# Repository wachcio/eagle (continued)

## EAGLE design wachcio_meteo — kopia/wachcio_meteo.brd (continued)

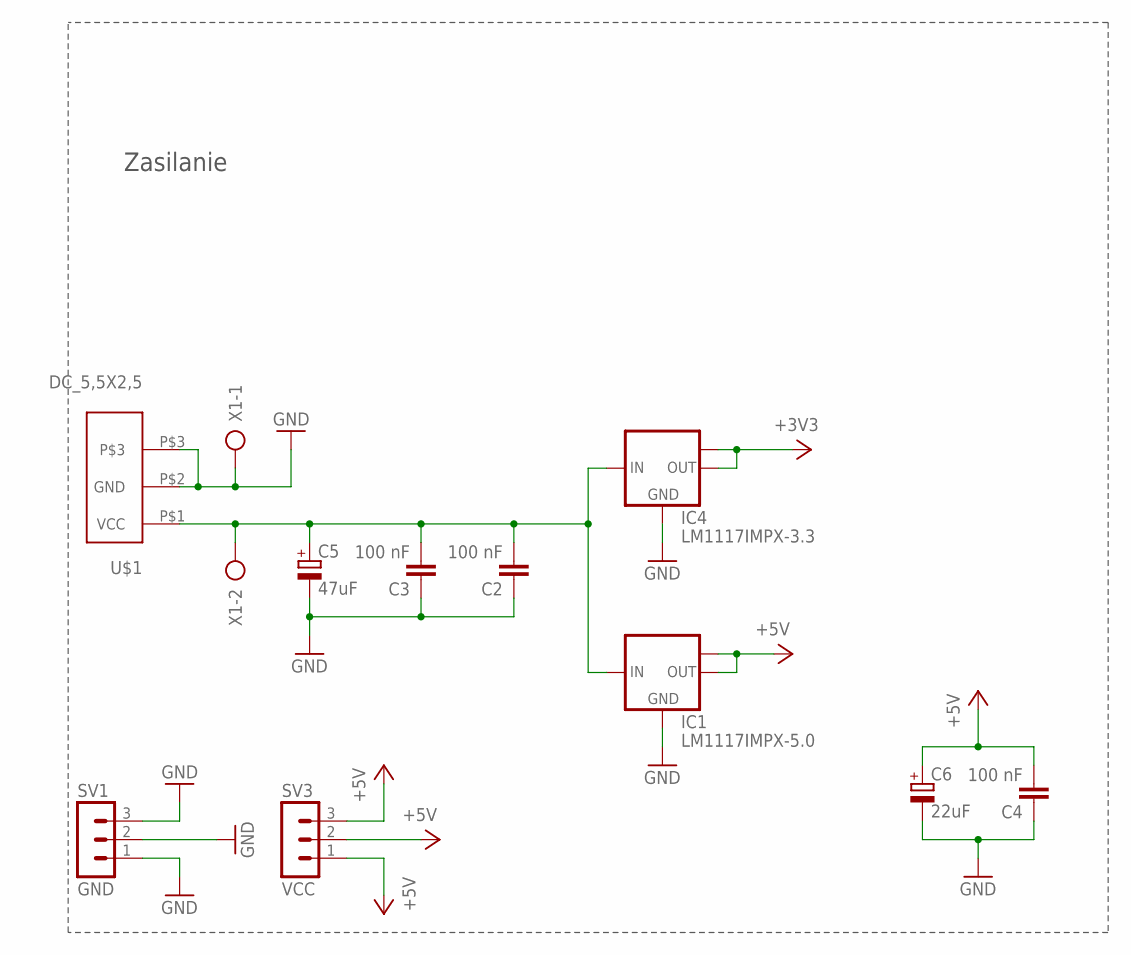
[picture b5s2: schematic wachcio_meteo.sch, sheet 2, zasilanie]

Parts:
C2, C3, C4: 100 nF; C0805
C5: 47uF; B45181A
C6: 22uF; B45181A
IC1: LM1117IMPX-5.0; SOT223
IC4: LM1117IMPX-3.3; SOT223
SV1: GND; MA03-1
SV3: VCC; MA03-1
U$1: DC_5,5X2,5
X1: AK500/2

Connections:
+3V3: IC4.2 (OUT), IC4.TAB (OUT1); also elsewhere on the board
+5V: C4.2, C6.+, IC1.2 (OUT), IC1.TAB (OUT1), SV3.1, SV3.2, SV3.3; also elsewhere on the board
+9V: C2.2, C3.2, C5.+, IC1.3 (IN), IC4.3 (IN), U$1.P$1 (VCC), X1.2
GND: C2.1, C3.1, C4.1, C5.-, C6.-, IC1.1 (GND), IC4.1 (GND), SV1.1, SV1.2, SV1.3, U$1.P$2 (GND), U$1.P$3, X1.1; also elsewhere on the board

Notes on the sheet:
Zasilanie

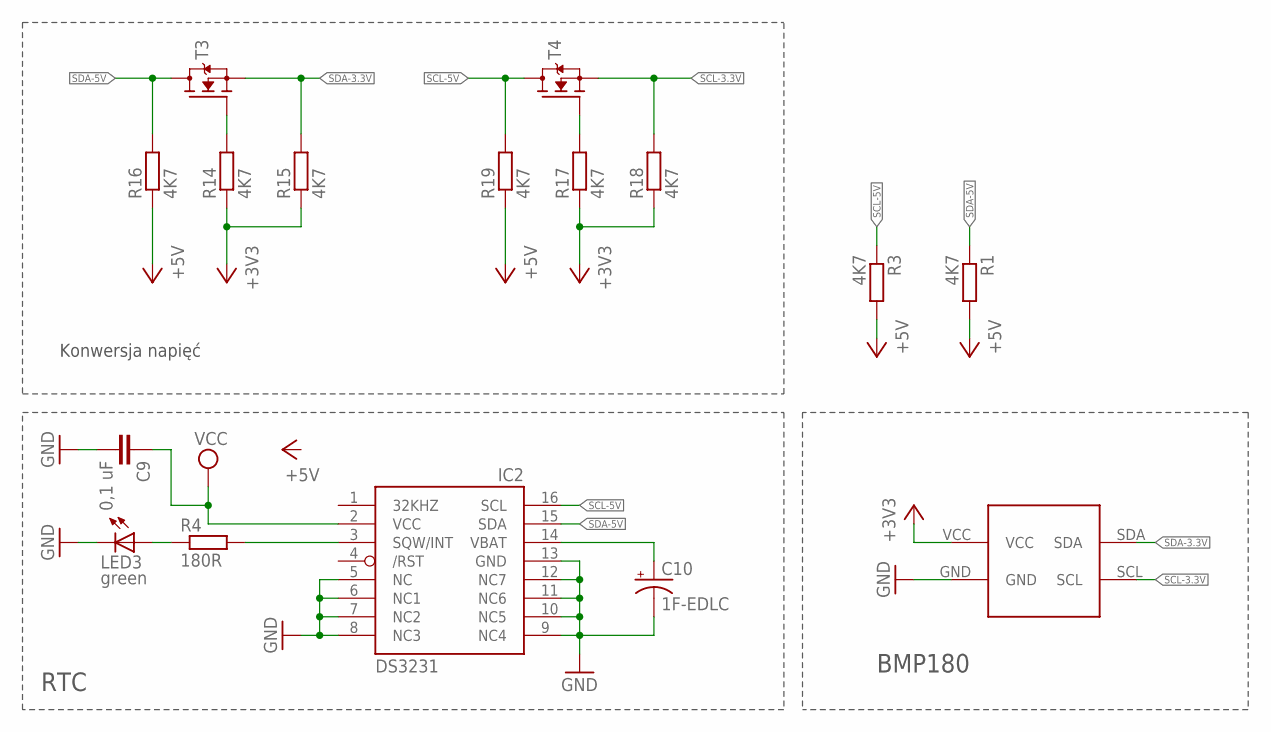
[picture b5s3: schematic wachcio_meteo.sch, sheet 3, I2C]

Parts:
C9: 0,1 uF; C0805
C10: 1F-EDLC; CAP-RADIAL-5MM-21.5MM
IC2: DS3231/SO; SO16W
LED3: green; CHIPLED_1206
R1, R3, R14, R15, R16, R17, R18, R19: 4K7; R1206W
R4: 180R; R1206W
T3, T4: MOSFET-N-SOT23; SOT23
U$3: BMP180

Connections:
+3V3: R14.1, R15.1, R17.1, R18.1, U$3.VCC; also elsewhere on the board
+5V: R1.2, R3.2, R16.1, R19.1; also elsewhere on the board
GND: C9.2, C10.-, IC2.5 (NC), IC2.6 (NC1), IC2.7 (NC2), IC2.8 (NC3), IC2.9 (NC4), IC2.10 (NC5), IC2.11 (NC6), IC2.12 (NC7), IC2.13 (GND), LED3.C, U$3.GND; also elsewhere on the board
unnamed: LED3.A, R4.1
unnamed: IC2.3 (SQW/INT), R4.2
unnamed: C10.+, IC2.14 (VBAT)
unnamed: R14.2, T3.1 (G)
unnamed: R17.2, T4.1 (G)
SCL-3.3V: R18.2, T4.2 (S), U$3.SCL
SCL-5V: IC2.16 (SCL), R3.1, R19.2, T4.3 (D)
SDA-3.3V: R15.2, T3.2 (S), U$3.SDA
SDA-5V: IC2.15 (SDA), R1.1, R16.2, T3.3 (D)
VCC: C9.1, IC2.2 (VCC)

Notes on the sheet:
Konwersja napięć
RTC
BMP180

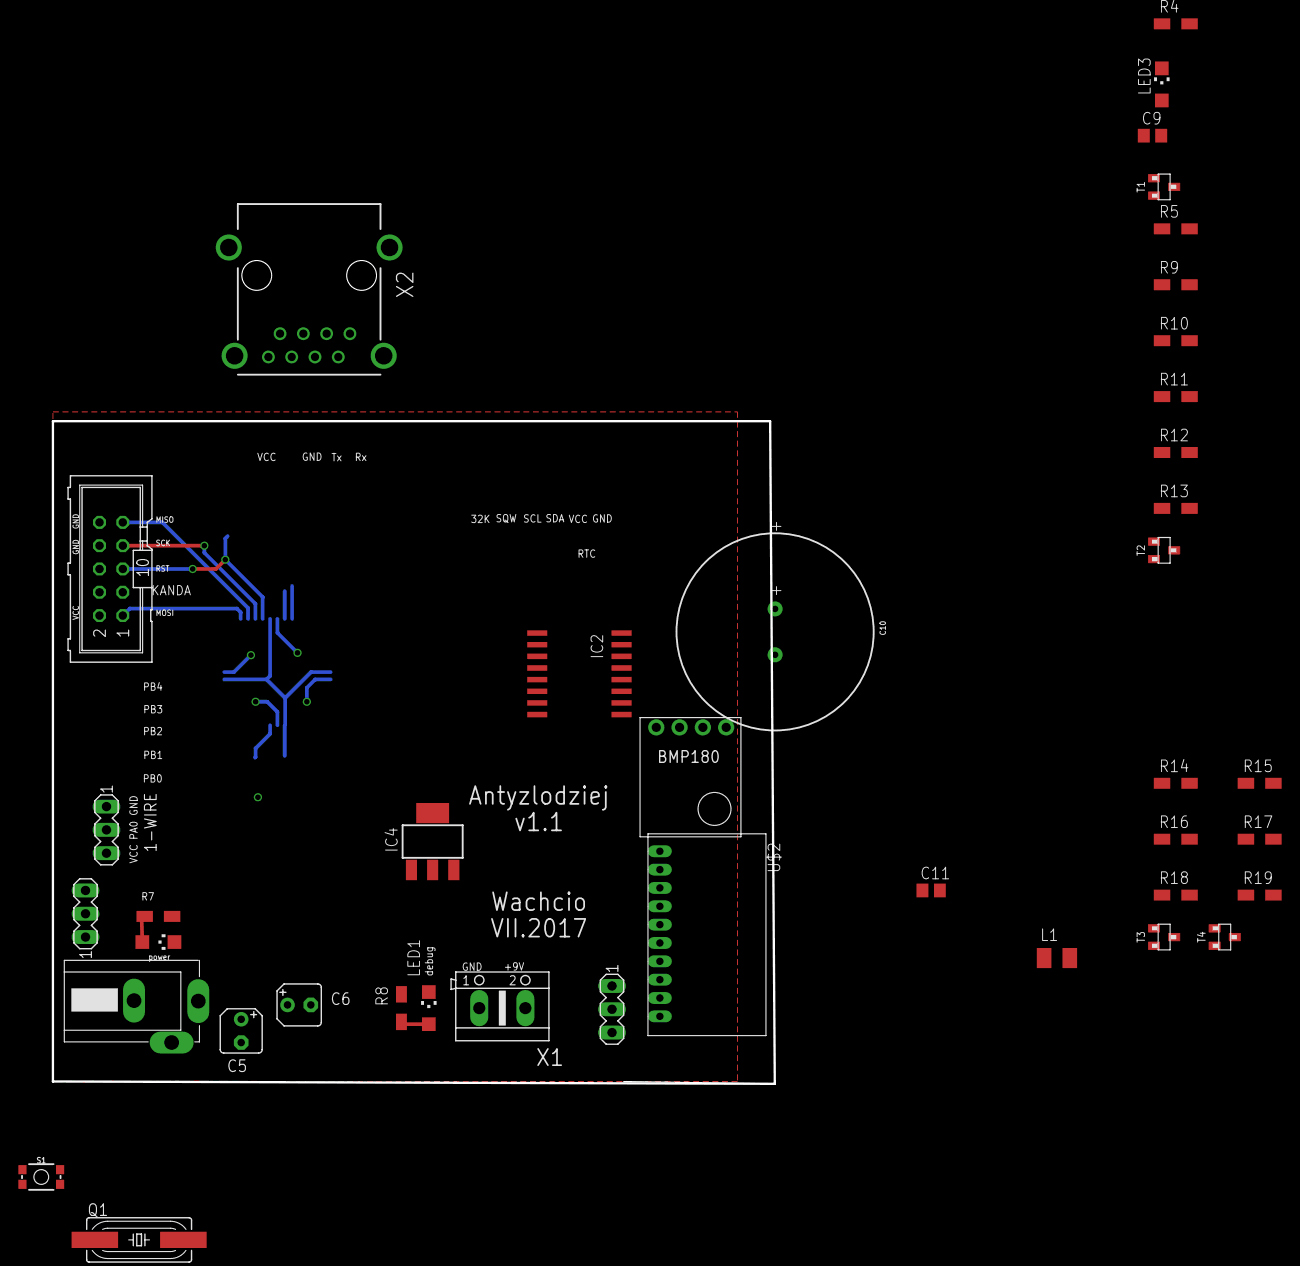
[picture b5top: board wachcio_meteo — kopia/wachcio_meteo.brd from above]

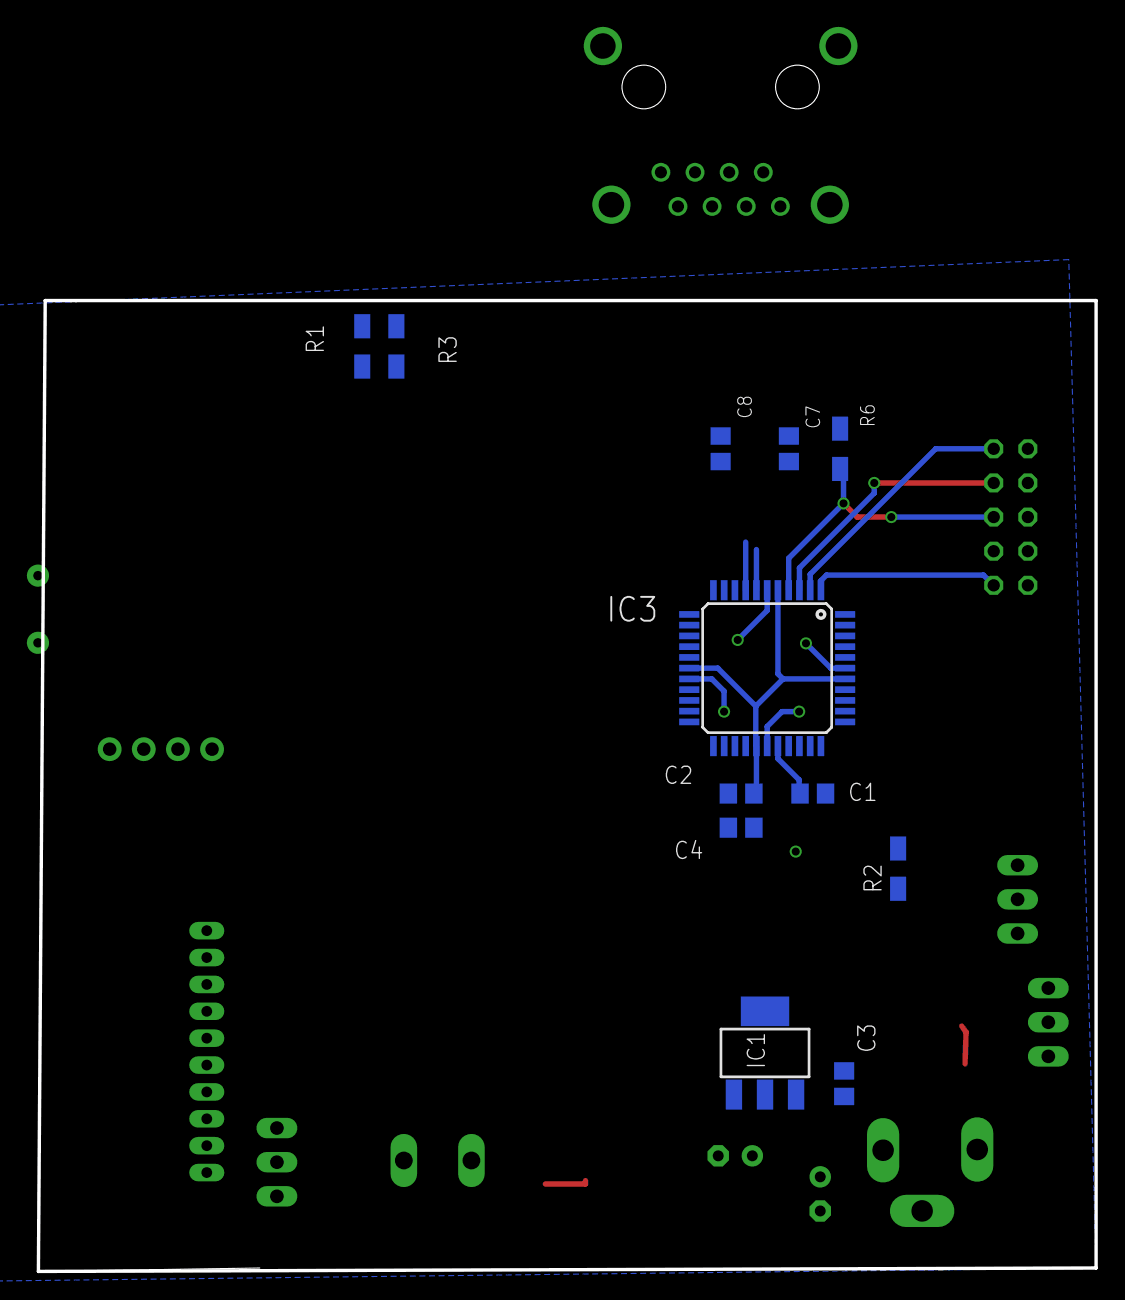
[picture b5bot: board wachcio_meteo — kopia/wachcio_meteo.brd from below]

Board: 2 copper layers, 78.7 x 72.2 mm, 53 parts (12 on the bottom side), 39 nets.

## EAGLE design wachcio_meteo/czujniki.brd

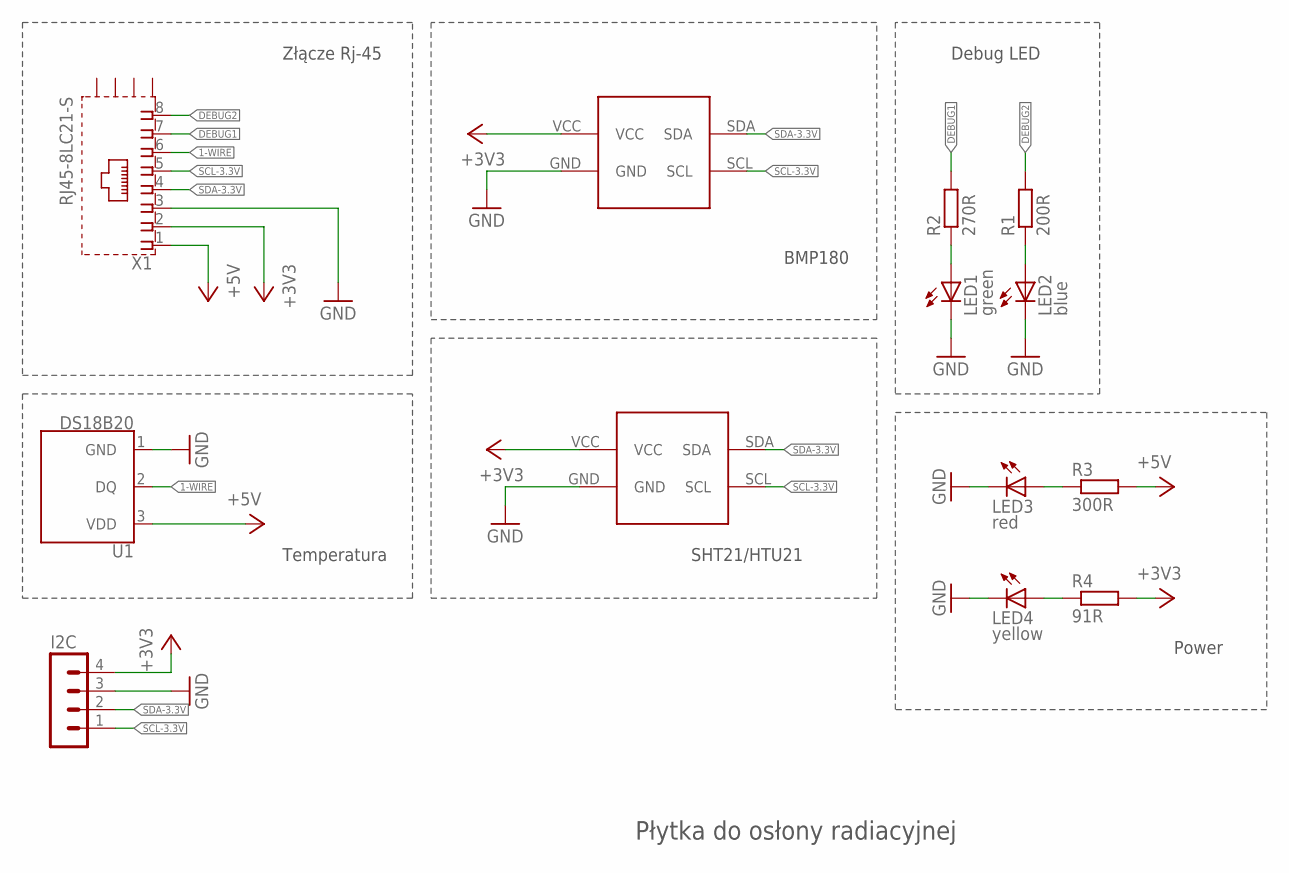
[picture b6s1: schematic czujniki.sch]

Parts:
I2C: MA04-1
LED1: green; CHIPLED_1206
LED2: blue; CHIPLED_1206
LED3: red; CHIPLED_1206
LED4: yellow; CHIPLED_1206
R1: 200R; M0805
R2: 270R; M0805
R3: 300R; M0805
R4: 91R; M0805
U1: DS18B20; TO-92-AMMO
U$1: BMP180
U$2: I2C_BOARD
X1: RJ45-8LC21-S; RJ45-SHIELD1

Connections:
1-WIRE: U1.2 (DQ), X1.6
+3V3: I2C.4, R4.2, U$1.VCC, U$2.VCC, X1.2
+5V: R3.2, U1.3 (VDD), X1.1
DEBUG1: R2.2, X1.7
DEBUG2: R1.2, X1.8
GND: I2C.3, LED1.C, LED2.C, LED3.C, LED4.C, U1.1 (GND), U$1.GND, U$2.GND, X1.3
unnamed: LED1.A, R2.1
unnamed: LED2.A, R1.1
unnamed: LED3.A, R3.1
unnamed: LED4.A, R4.1
SCL-3.3V: I2C.1, U$1.SCL, U$2.SCL, X1.5
SDA-3.3V: I2C.2, U$1.SDA, U$2.SDA, X1.4

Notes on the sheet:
BMP180
SHT21/HTU21
Złącze Rj-45
Temperatura
Debug LED
Płytka do osłony radiacyjnej
Power

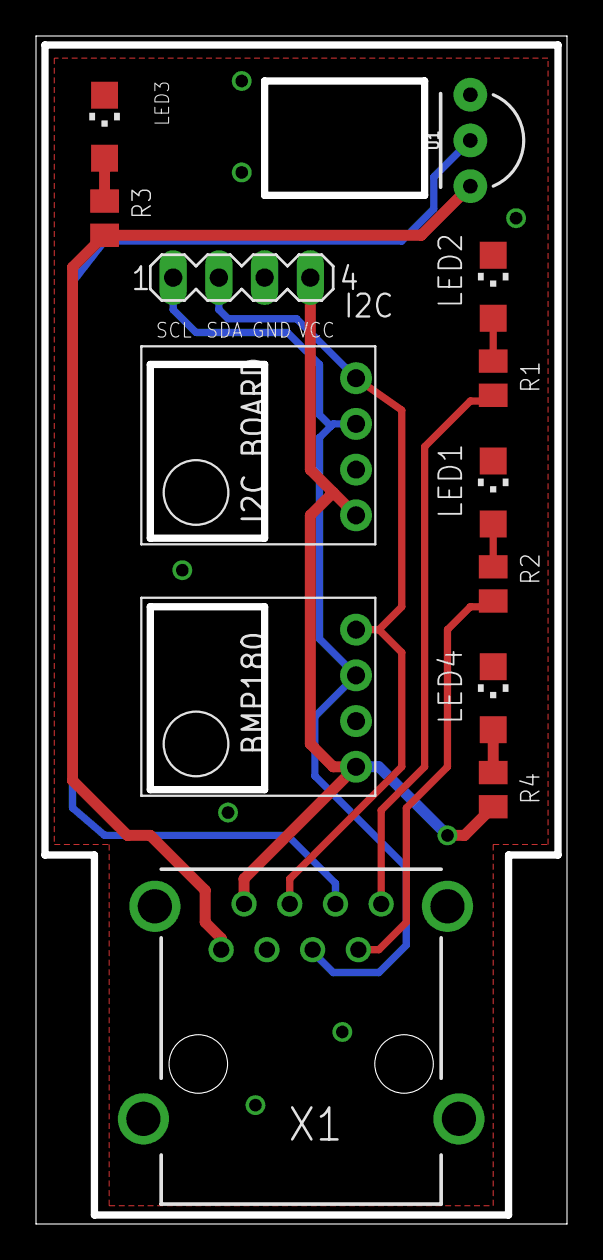
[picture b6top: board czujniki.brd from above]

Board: 2 copper layers, 29.5 x 66.0 mm, 13 parts (0 on the bottom side), 12 nets.

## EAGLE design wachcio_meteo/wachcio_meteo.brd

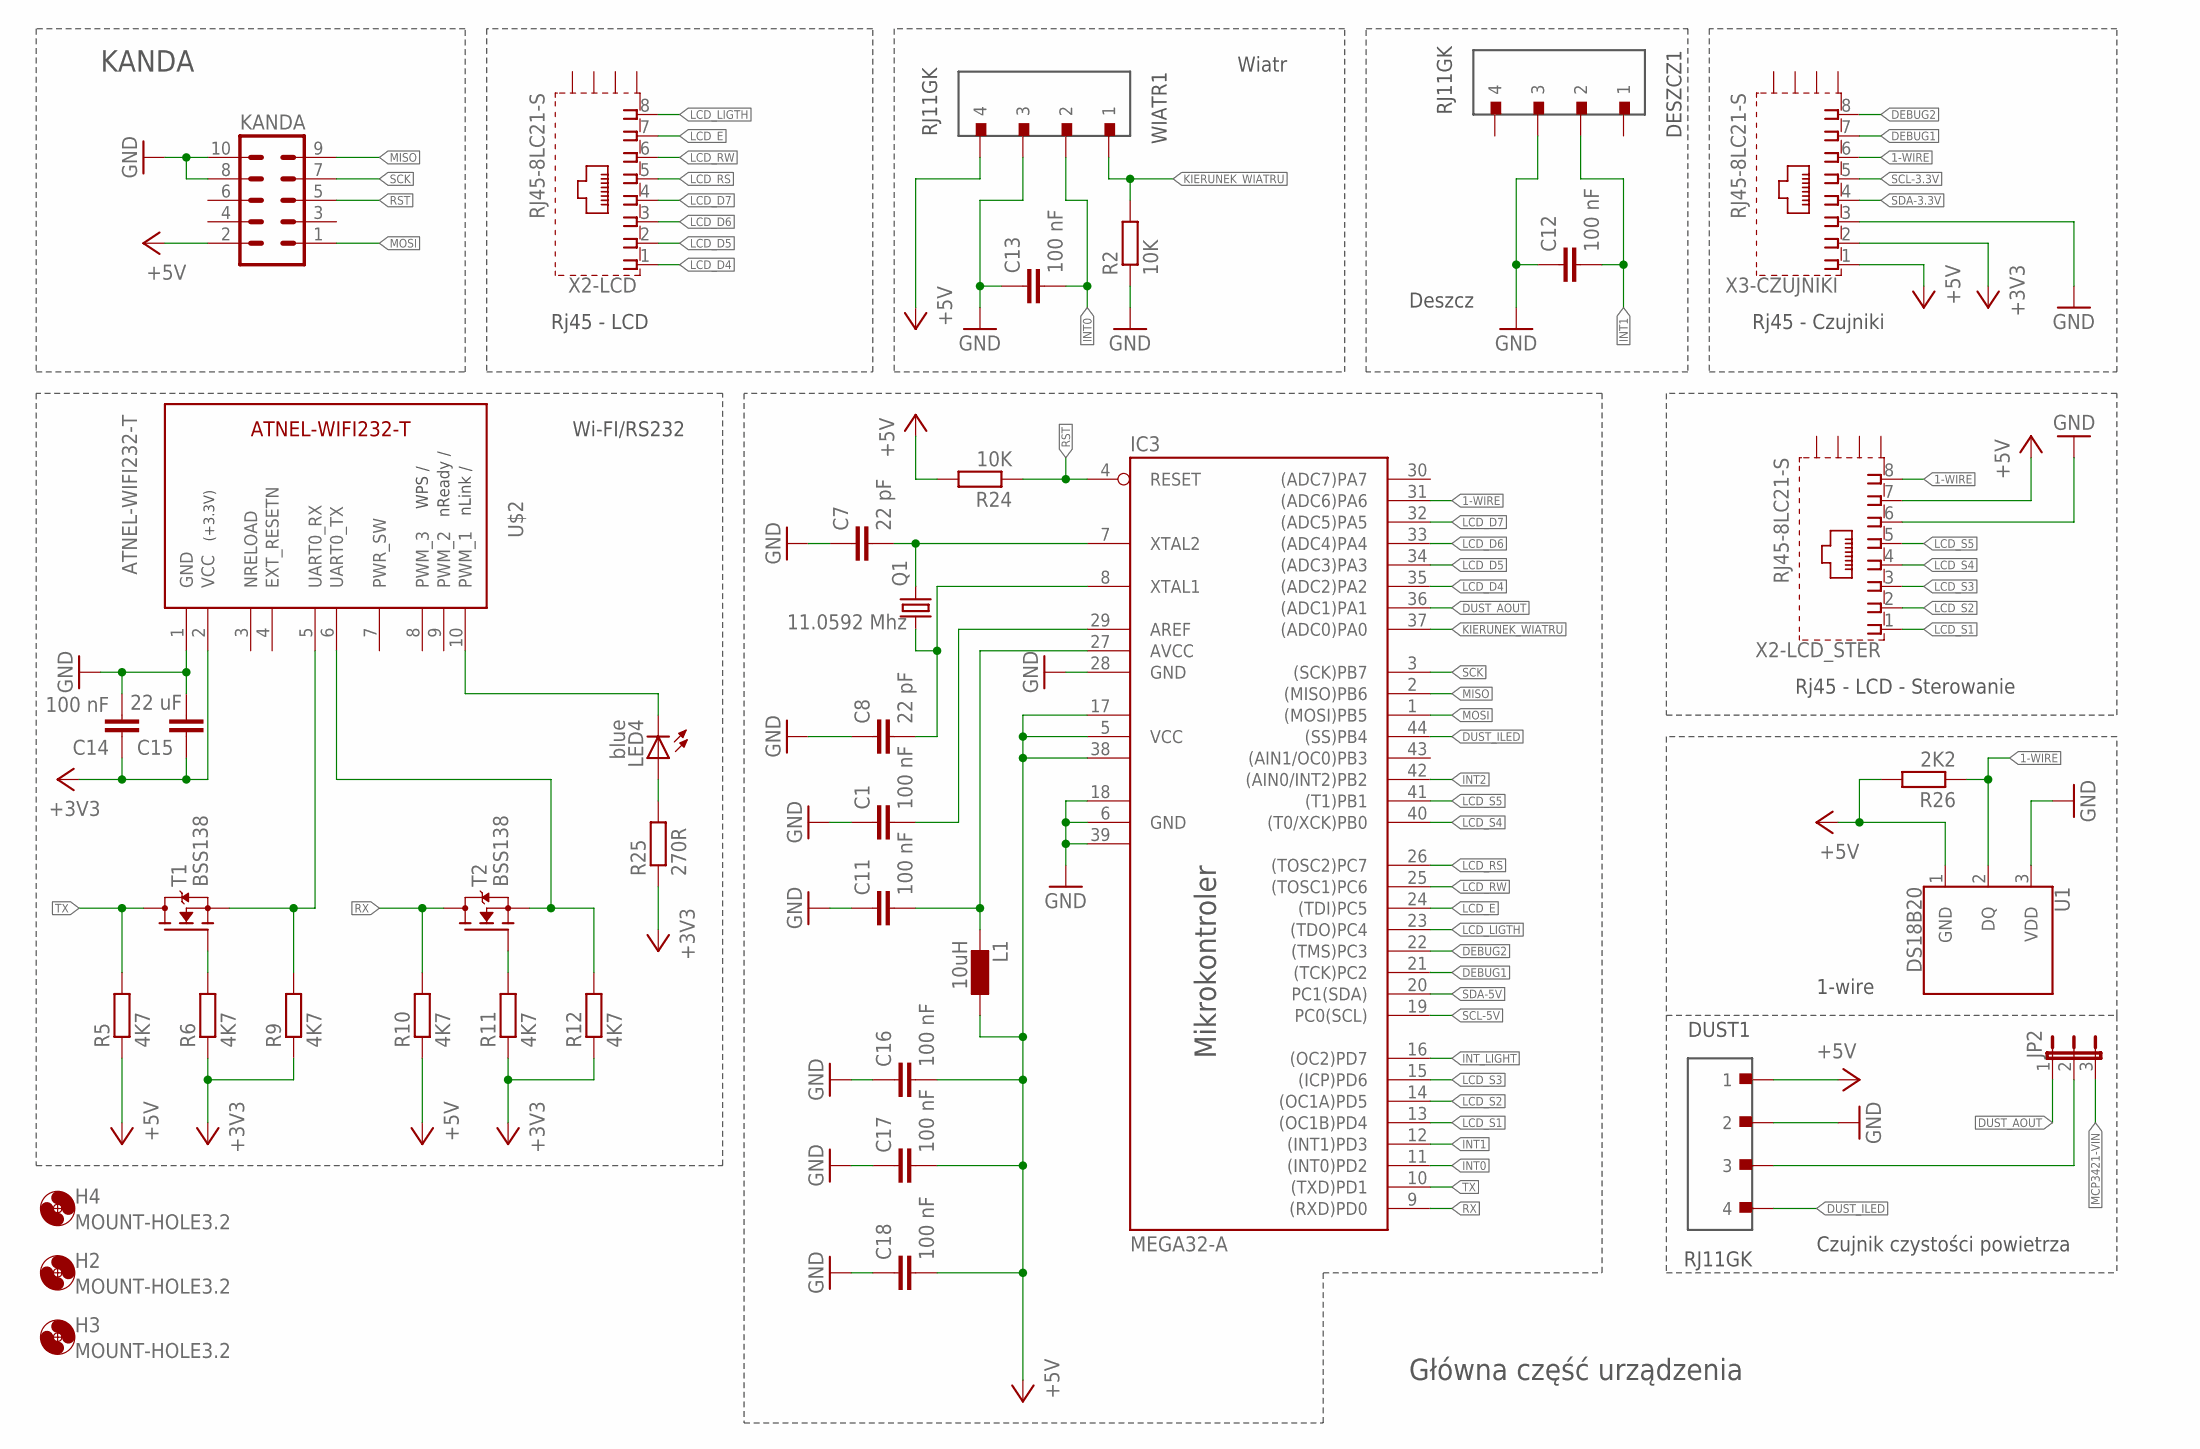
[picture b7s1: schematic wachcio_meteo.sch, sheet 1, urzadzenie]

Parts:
C1, C11, C12, C13, C14, C16, C17, C18: 100 nF; C0805
C7, C8: 22 pF; C0805
C15: 22 uF; C0805
DESZCZ1: RJ11GK
DUST1: RJ11GK
H2, H3, H4: MOUNT-HOLE3.2; 3,2
IC3: MEGA32-A; TQFP44
JP2: JP2E; JP2
KANDA: ML10
L1: 10uH; L3230M
LED4: blue; CHIPLED_1206
Q1: 11.0592 Mhz; SM49
R2, R24: 10K; M0805
R5, R6, R9, R10, R11, R12: 4K7; M0805
R25: 270R; M0805
R26: 2K2; M0805
T1, T2: BSS138; SOT23
U1: DS18B20; TO-92-AMMO
U$2: ATNEL-WIFI232-T
WIATR1: RJ11GK
X2-LCD, X2-LCD_STER, X3-CZUJNIKI: RJ45-8LC21-S; RJ45-SHIELD1

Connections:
1-WIRE: IC3.31 ((ADC6)PA6), R26.1, U1.2 (DQ), X2-LCD_STER.8, X3-CZUJNIKI.6
+3V3: C14.1, C15.1, R6.1, R9.1, R11.1, R12.1, R25.1, U$2.2 (VCC), X3-CZUJNIKI.2; also elsewhere on the board
+5V: C16.2, C17.2, C18.2, DUST1.1, IC3.5 (VCC), IC3.17 (VCC1), IC3.38 (VCC2), KANDA.2, L1.1, R5.1, R10.1, R24.2, R26.2, U1.1 (GND), WIATR1.4, X2-LCD_STER.7, X3-CZUJNIKI.1; also elsewhere on the board
DEBUG1: IC3.21 ((TCK)PC2), X3-CZUJNIKI.7
DEBUG2: IC3.22 ((TMS)PC3), X3-CZUJNIKI.8
DUST_AOUT: IC3.36 ((ADC1)PA1), JP2.1
DUST_ILED: DUST1.4, IC3.44 ((SS)PB4)
GND: C1.1, C7.1, C8.1, C11.1, C12.1, C13.1, C14.2, C15.2, C16.1, C17.1, C18.1, DESZCZ1.3, DUST1.2, IC3.6 (GND), IC3.18 (GND1), IC3.28 (GND), IC3.39 (GND2), KANDA.8, KANDA.10, R2.1, U1.3 (VDD), U$2.1 (GND), WIATR1.3, X2-LCD_STER.6, X3-CZUJNIKI.3; also elsewhere on the board
INT0: C13.2, IC3.11 ((INT0)PD2), WIATR1.2
INT1: C12.2, DESZCZ1.2, IC3.12 ((INT1)PD3)
INT2: IC3.42 ((AIN0/INT2)PB2); also elsewhere on the board
INT_LIGHT: IC3.16 ((OC2)PD7); also elsewhere on the board
KIERUNEK_WIATRU: IC3.37 ((ADC0)PA0), R2.2, WIATR1.1
LCD_D4: IC3.35 ((ADC2)PA2), X2-LCD.1
LCD_D5: IC3.34 ((ADC3)PA3), X2-LCD.2
LCD_D6: IC3.33 ((ADC4)PA4), X2-LCD.3
LCD_D7: IC3.32 ((ADC5)PA5), X2-LCD.4
LCD_E: IC3.24 ((TDI)PC5), X2-LCD.7
LCD_LIGTH: IC3.23 ((TDO)PC4), X2-LCD.8
LCD_RS: IC3.26 ((TOSC2)PC7), X2-LCD.5
LCD_RW: IC3.25 ((TOSC1)PC6), X2-LCD.6
LCD_S1: IC3.13 ((OC1B)PD4), X2-LCD_STER.1
LCD_S2: IC3.14 ((OC1A)PD5), X2-LCD_STER.2
LCD_S3: IC3.15 ((ICP)PD6), X2-LCD_STER.3
LCD_S4: IC3.40 ((T0/XCK)PB0), X2-LCD_STER.4
LCD_S5: IC3.41 ((T1)PB1), X2-LCD_STER.5
MCP3421-VIN: JP2.3; also elsewhere on the board
MISO: IC3.2 ((MISO)PB6), KANDA.9
MOSI: IC3.1 ((MOSI)PB5), KANDA.1
unnamed: R9.2, T1.2 (S), U$2.5 (UART0_RX)
unnamed: C11.2, IC3.27 (AVCC), L1.2
unnamed: C1.2, IC3.29 (AREF)
unnamed: LED4.A, R25.2
unnamed: R6.2, T1.1 (G)
unnamed: LED4.C, U$2.10 (PWM_1)
unnamed: R12.2, T2.2 (S), U$2.6 (UART0_TX)
unnamed: C7.2, IC3.7 (XTAL2), Q1.2
unnamed: C8.2, IC3.8 (XTAL1), Q1.1
unnamed: DUST1.3, JP2.2
unnamed: R11.2, T2.1 (G)
RST: IC3.4 (RESET), KANDA.5, R24.1
RX: IC3.9 ((RXD)PD0), R10.2, T2.3 (D)
SCK: IC3.3 ((SCK)PB7), KANDA.7
SCL-3.3V: X3-CZUJNIKI.5; also elsewhere on the board
SCL-5V: IC3.19 (PC0(SCL)); also elsewhere on the board
SDA-3.3V: X3-CZUJNIKI.4; also elsewhere on the board
SDA-5V: IC3.20 (PC1(SDA)); also elsewhere on the board
TX: IC3.10 ((TXD)PD1), R5.2, T1.3 (D)

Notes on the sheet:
KANDA
Mikrokontroler
Rj45 - LCD
Wiatr
Deszcz
Rj45 - Czujniki
Wi-FI/RS232
1-wire
Rj45 - LCD - Sterowanie
Główna część urządzenia
Czujnik czystości powietrza

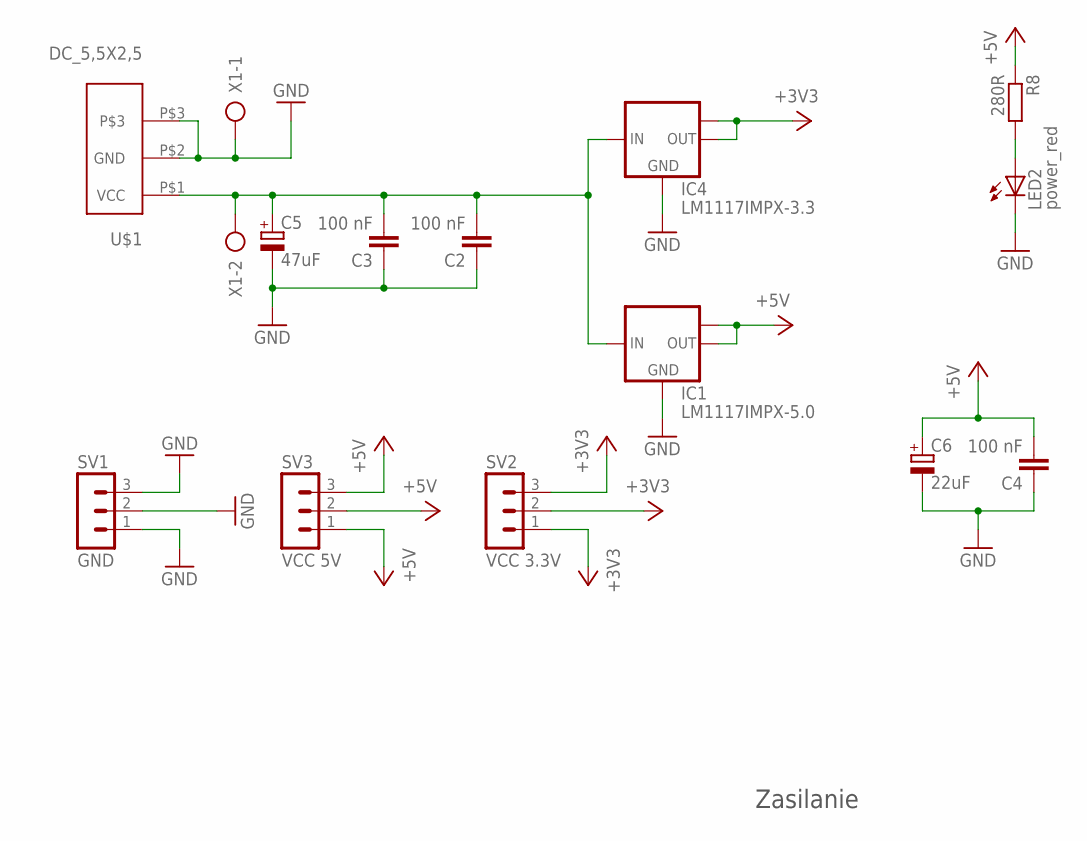
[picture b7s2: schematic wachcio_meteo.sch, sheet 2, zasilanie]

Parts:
C2, C3, C4: 100 nF; C0805
C5: 47uF; B45181A
C6: 22uF; B45181A
IC1: LM1117IMPX-5.0; SOT223
IC4: LM1117IMPX-3.3; SOT223
LED2: power_red; CHIPLED_1206
R8: 280R; M0805
SV1: GND; MA03-1
SV2: VCC 3.3V; MA03-1
SV3: VCC 5V; MA03-1
U$1: DC_5,5X2,5
X1: AK500/2

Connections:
+3V3: IC4.2 (OUT), IC4.TAB (OUT1), SV2.1, SV2.2, SV2.3; also elsewhere on the board
+5V: C4.2, C6.+, IC1.2 (OUT), IC1.TAB (OUT1), R8.1, SV3.1, SV3.2, SV3.3; also elsewhere on the board
+9V: C2.2, C3.2, C5.+, IC1.3 (IN), IC4.3 (IN), U$1.P$1 (VCC), X1.2
GND: C2.1, C3.1, C4.1, C5.-, C6.-, IC1.1 (GND), IC4.1 (GND), LED2.C, SV1.1, SV1.2, SV1.3, U$1.P$2 (GND), U$1.P$3, X1.1; also elsewhere on the board
unnamed: LED2.A, R8.2

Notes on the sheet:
Zasilanie

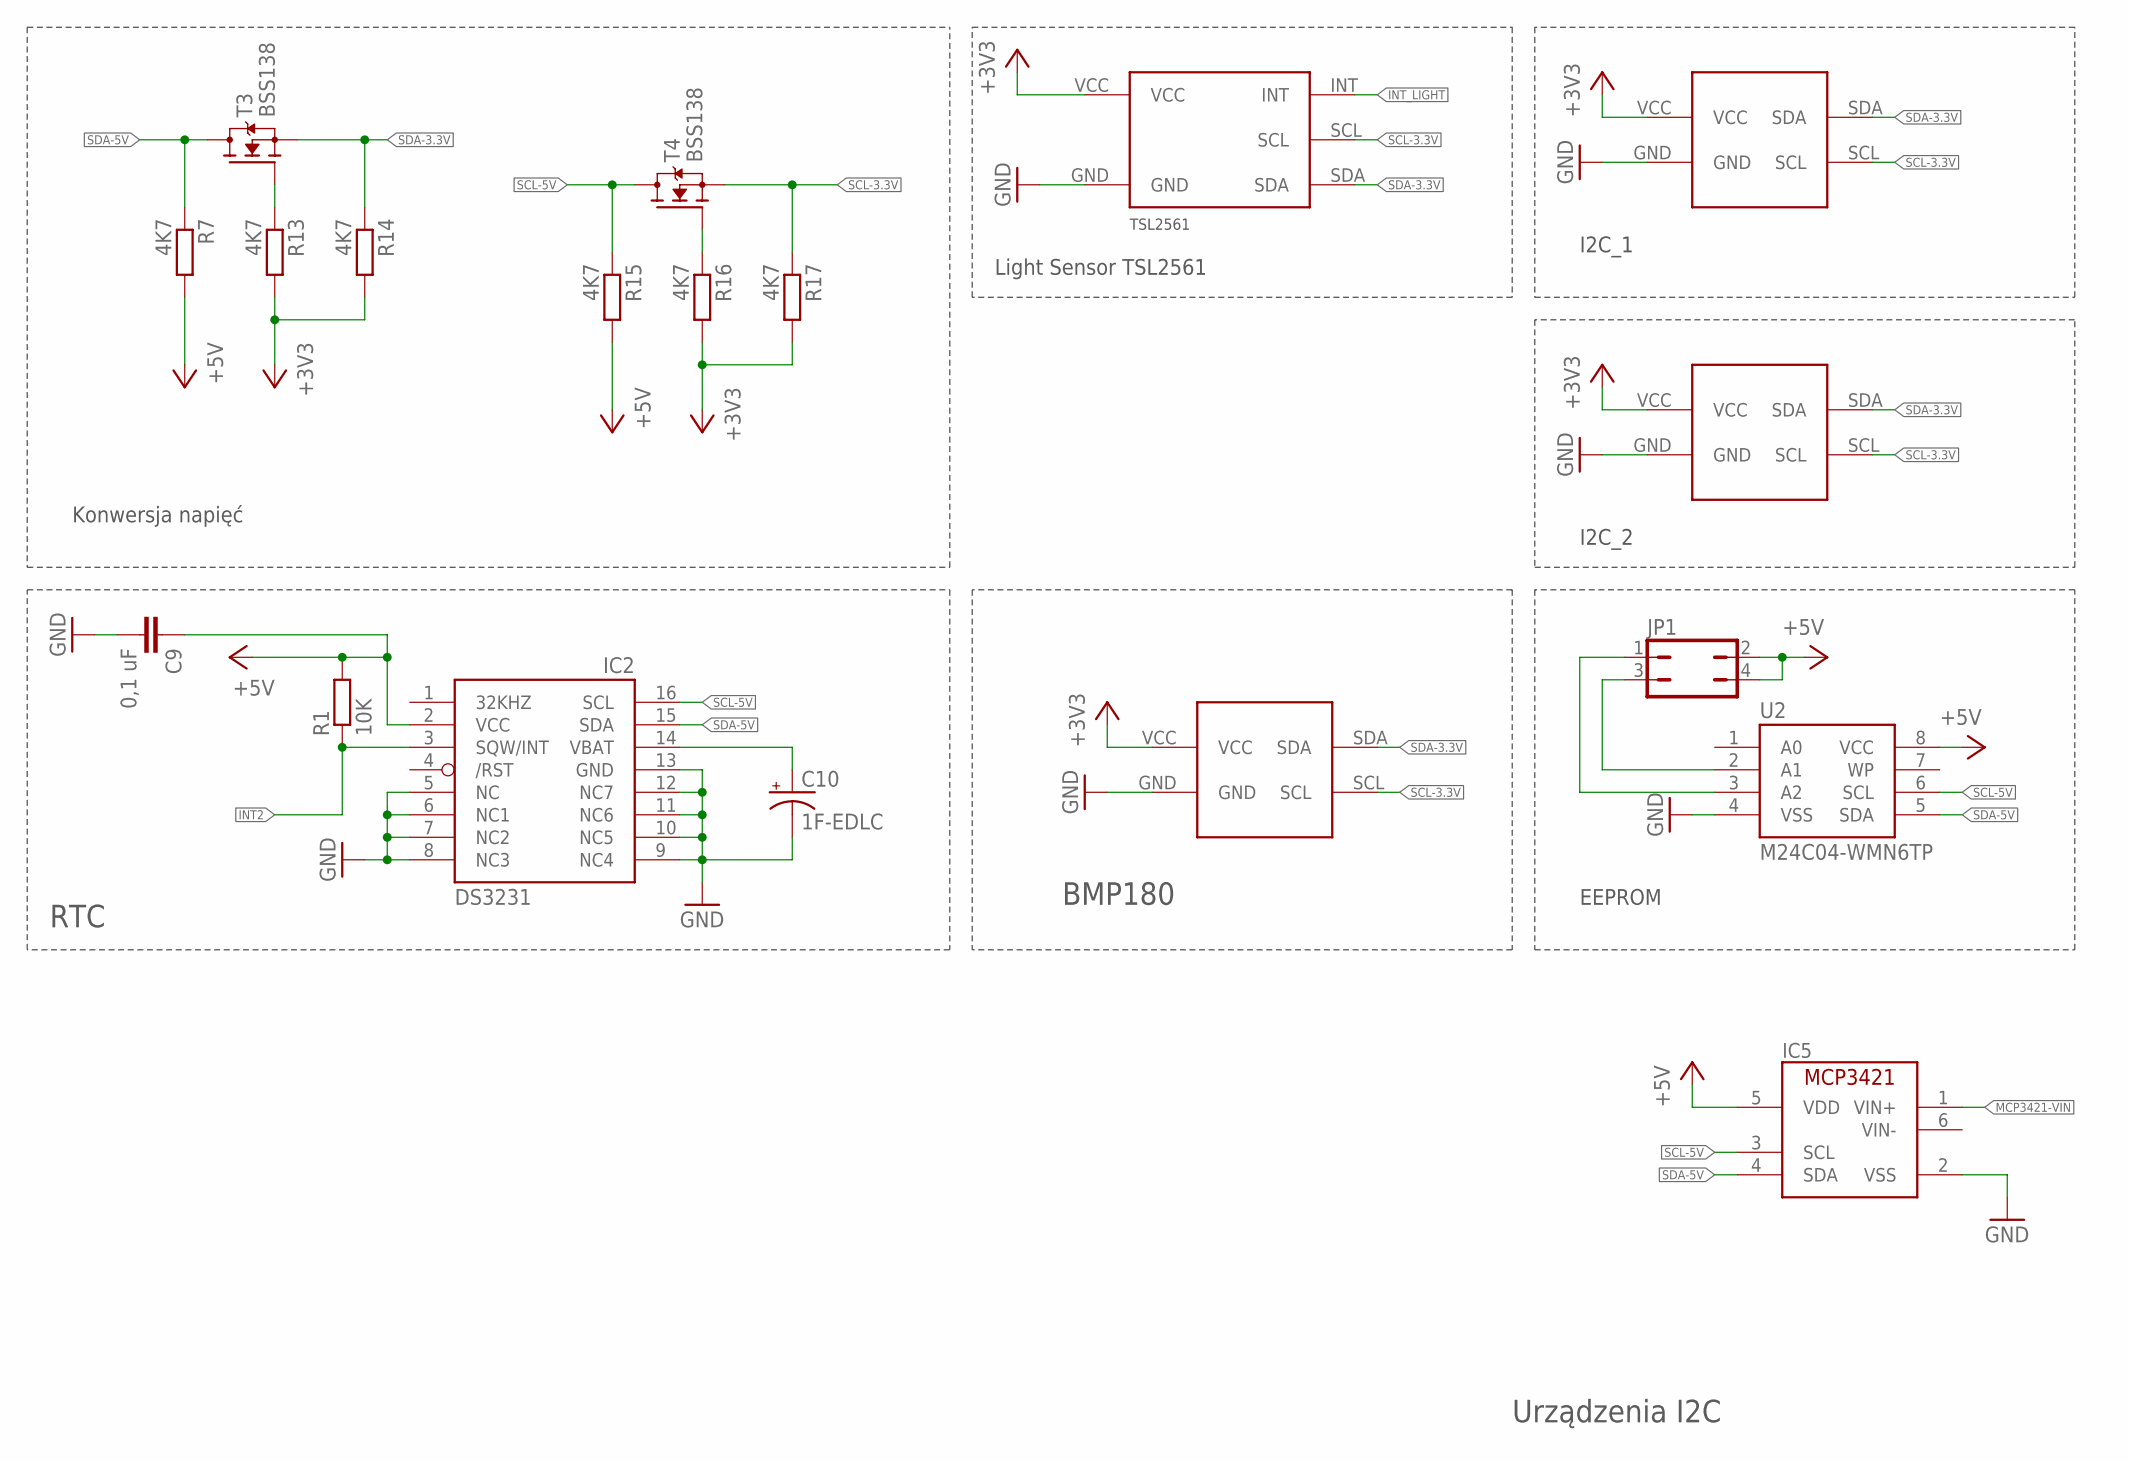
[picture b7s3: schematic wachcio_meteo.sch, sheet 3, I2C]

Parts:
C9: 0,1 uF; C0805
C10: 1F-EDLC; CAP-RADIAL-5MM-21.5MM
IC2: DS3231/SO; SO16W
IC5: MCP3421; SOT-23
JP1: JP2Q
R1: 10K; M0805
R7, R13, R14, R15, R16, R17: 4K7; M0805
T3, T4: BSS138; SOT23
U2: M24C04-WMN6TP; SO08
U$3: BMP180
U$5, U$6: I2C_BOARD
U$7: TSL2561GY-2561; TSL2561

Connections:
+3V3: R13.2, R14.2, R16.2, R17.2, U$3.VCC, U$5.VCC, U$6.VCC, U$7.VCC; also elsewhere on the board
+5V: C9.1, IC2.2 (VCC), IC5.5 (VDD), JP1.2, JP1.4, R1.2, R7.2, R15.2, U2.8 (VCC); also elsewhere on the board
GND: C9.2, C10.-, IC2.5 (NC), IC2.6 (NC1), IC2.7 (NC2), IC2.8 (NC3), IC2.9 (NC4), IC2.10 (NC5), IC2.11 (NC6), IC2.12 (NC7), IC2.13 (GND), IC5.2 (VSS), U2.4 (VSS), U$3.GND, U$5.GND, U$6.GND, U$7.GND; also elsewhere on the board
INT2: IC2.3 (SQW/INT), R1.1; also elsewhere on the board
INT_LIGHT: U$7.INT; also elsewhere on the board
MCP3421-VIN: IC5.1 (VIN+); also elsewhere on the board
unnamed: C10.+, IC2.14 (VBAT)
unnamed: R13.1, T3.1 (G)
unnamed: R16.1, T4.1 (G)
unnamed: JP1.3, U2.2 (A1)
unnamed: JP1.1, U2.3 (A2)
SCL-3.3V: R17.1, T4.2 (S), U$3.SCL, U$5.SCL, U$6.SCL, U$7.SCL; also elsewhere on the board
SCL-5V: IC2.16 (SCL), IC5.3 (SCL), R15.1, T4.3 (D), U2.6 (SCL); also elsewhere on the board
SDA-3.3V: R14.1, T3.2 (S), U$3.SDA, U$5.SDA, U$6.SDA, U$7.SDA; also elsewhere on the board
SDA-5V: IC2.15 (SDA), IC5.4 (SDA), R7.1, T3.3 (D), U2.5 (SDA); also elsewhere on the board

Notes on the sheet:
Konwersja napięć
RTC
BMP180
I2C_1
I2C_2
EEPROM
Light Sensor TSL2561
Urządzenia I2C

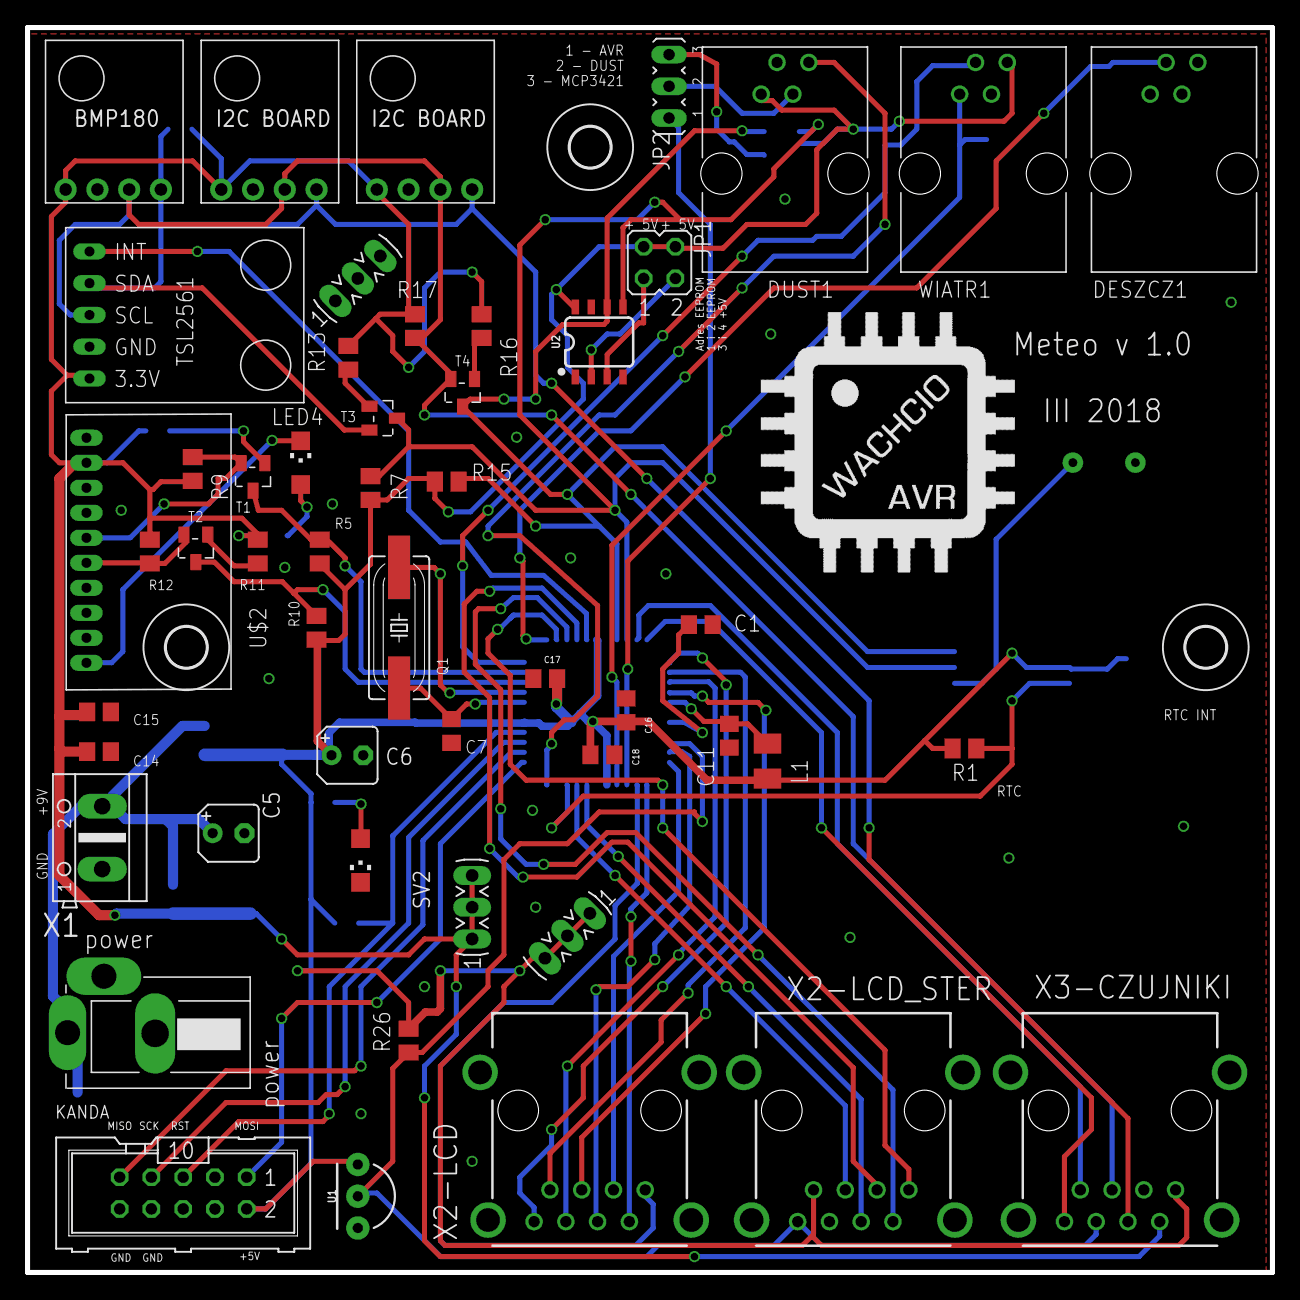
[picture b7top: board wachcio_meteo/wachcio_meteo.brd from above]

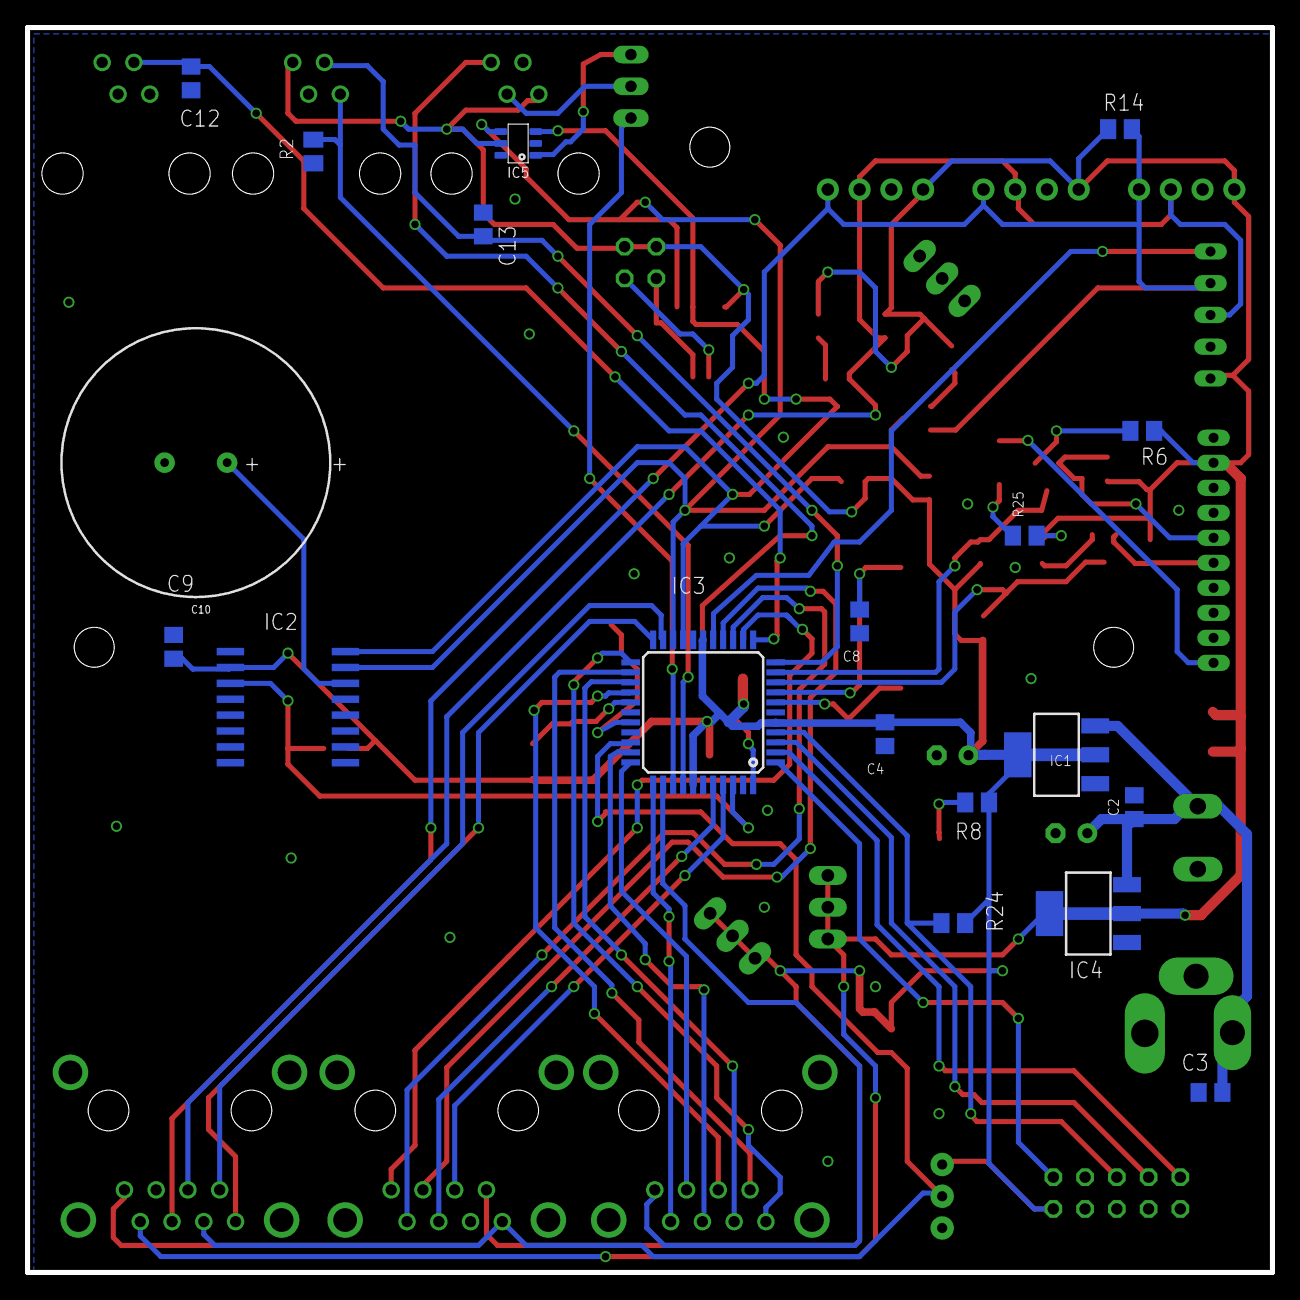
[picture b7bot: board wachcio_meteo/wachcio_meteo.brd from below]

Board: 2 copper layers, 99.6 x 99.6 mm, 74 parts (19 on the bottom side), 55 nets.

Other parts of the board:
U$8: LOGO
